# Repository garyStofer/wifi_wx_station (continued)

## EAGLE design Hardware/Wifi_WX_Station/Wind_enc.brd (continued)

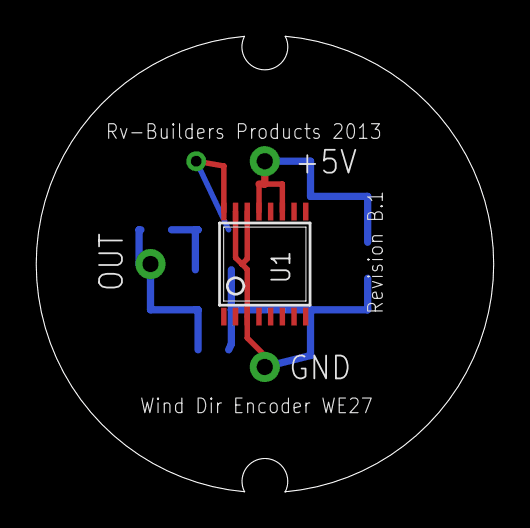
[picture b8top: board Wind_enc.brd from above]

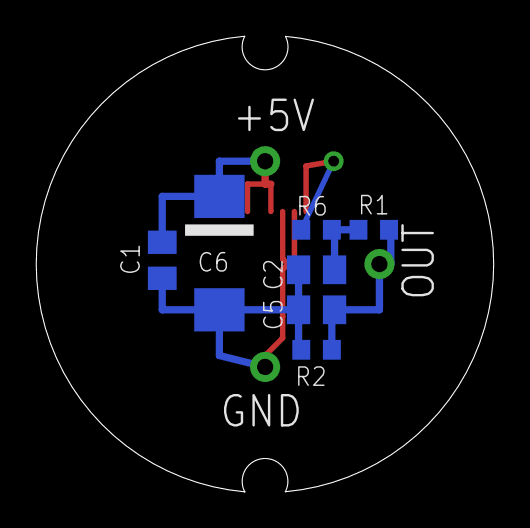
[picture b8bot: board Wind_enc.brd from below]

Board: 2 copper layers, 25.4 x 25.3 mm, 11 parts (7 on the bottom side), 5 nets.
